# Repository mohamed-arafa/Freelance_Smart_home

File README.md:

# Freelance_Smart_home
Arduino Nano code &amp; PCB design

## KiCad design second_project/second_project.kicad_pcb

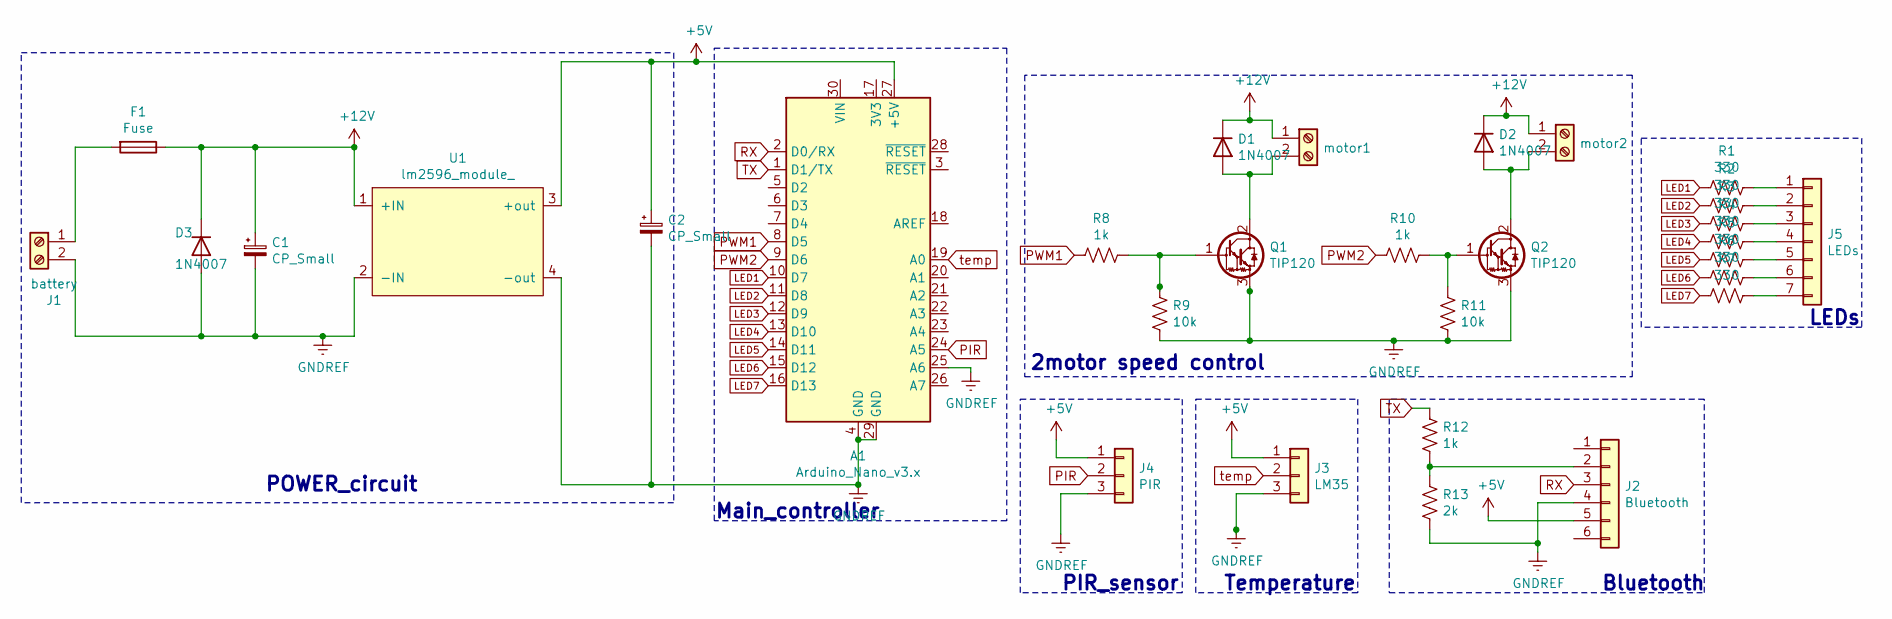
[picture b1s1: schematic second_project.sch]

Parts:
A1: Arduino_Nano_v3.x; Arduino_Nano
C1, C2: CP_Small; CP_Radial_D8.0mm_P3.80mm
D1, D2, D3: 1N4007; D_DO-41_SOD81_P10.16mm_Horizontal
F1: Fuse; Fuse_clips_20x5_pair
J1: battery; TerminalBlock_Phoenix_MKDS-1,5-2-5.08_1x02_P5.08mm_Horizont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
J2: Bluetooth; PinSocket_1x06_P2.54mm_Vertical
J3: LM35; PinSocket_1x03_P2.54mm_Vertical
J4: PIR; PinSocket_1x03_P2.54mm_Vertical
J5: LEDs; PinHeader_1x07_P2.54mm_Vertical
Q1, Q2: TIP120; TO-220-3_Vertical
R1, R2, R3, R4, R5, R6, R7: 330; R_Axial_DIN0207_L6.3mm_D2.5mm_P10.16mm_Horizontal
R8, R10, R12: 1k; R_Axial_DIN0207_L6.3mm_D2.5mm_P10.16mm_Horizontal
R9, R11: 10k; R_Axial_DIN0207_L6.3mm_D2.5mm_P10.16mm_Horizontal
R13: 2k; R_Axial_DIN0207_L6.3mm_D2.5mm_P10.16mm_Horizontal
U1: lm2596_module_; lm2596
motor1, motor2: Screw_Terminal_01x02; TerminalBlock_Phoenix_MKDS-1,5-2-5.08_1x02_P5.08mm_Horizont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

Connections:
+5V: A1.27 (+5V), C2.1, J2.5, J3.1, J4.1, U1.3 (+out)
+12V: C1.1, D1.1 (K), D2.1 (K), D3.1 (K), F1.1, U1.1 (+IN), motor1.1, motor2.1
GNDREF: A1.4 (GND), A1.25 (A6), A1.29 (GND), C1.2, C2.2, D3.2 (A), J1.2, J2.4, J3.3, J4.3, Q1.3 (E), Q2.3 (E), R9.1, R11.1, R13.2, U1.2 (-IN), U1.4 (-out)
LED1: A1.10 (D7), R1.2
LED2: A1.11 (D8), R2.2
LED3: A1.12 (D9), R3.2
LED4: A1.13 (D10), R4.2
LED5: A1.14 (D11), R5.2
LED6: A1.15 (D12), R6.2
LED7: A1.16 (D13), R7.2
unnamed: D1.2 (A), Q1.2 (C), motor1.2
unnamed: D2.2 (A), Q2.2 (C), motor2.2
unnamed: F1.2, J1.1
unnamed: J2.2, R12.2, R13.1
unnamed: J5.1, R1.1
unnamed: J5.2, R2.1
unnamed: J5.3, R3.1
unnamed: J5.4, R4.1
unnamed: J5.5, R5.1
unnamed: J5.6, R6.1
unnamed: J5.7, R7.1
unnamed: Q1.1 (B), R8.1, R9.2
unnamed: Q2.1 (B), R10.1, R11.2
PIR: A1.24 (A5), J4.2
PWM1: A1.8 (D5), R8.2
PWM2: A1.9 (D6), R10.2
RX: A1.2 (D0/RX), J2.3
TX: A1.1 (D1/TX), R12.1
temp: A1.19 (A0), J3.2

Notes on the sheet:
Bluetooth
2motor speed control
Temperature
PIR_sensor
POWER_circuit
Main_controller
LEDs

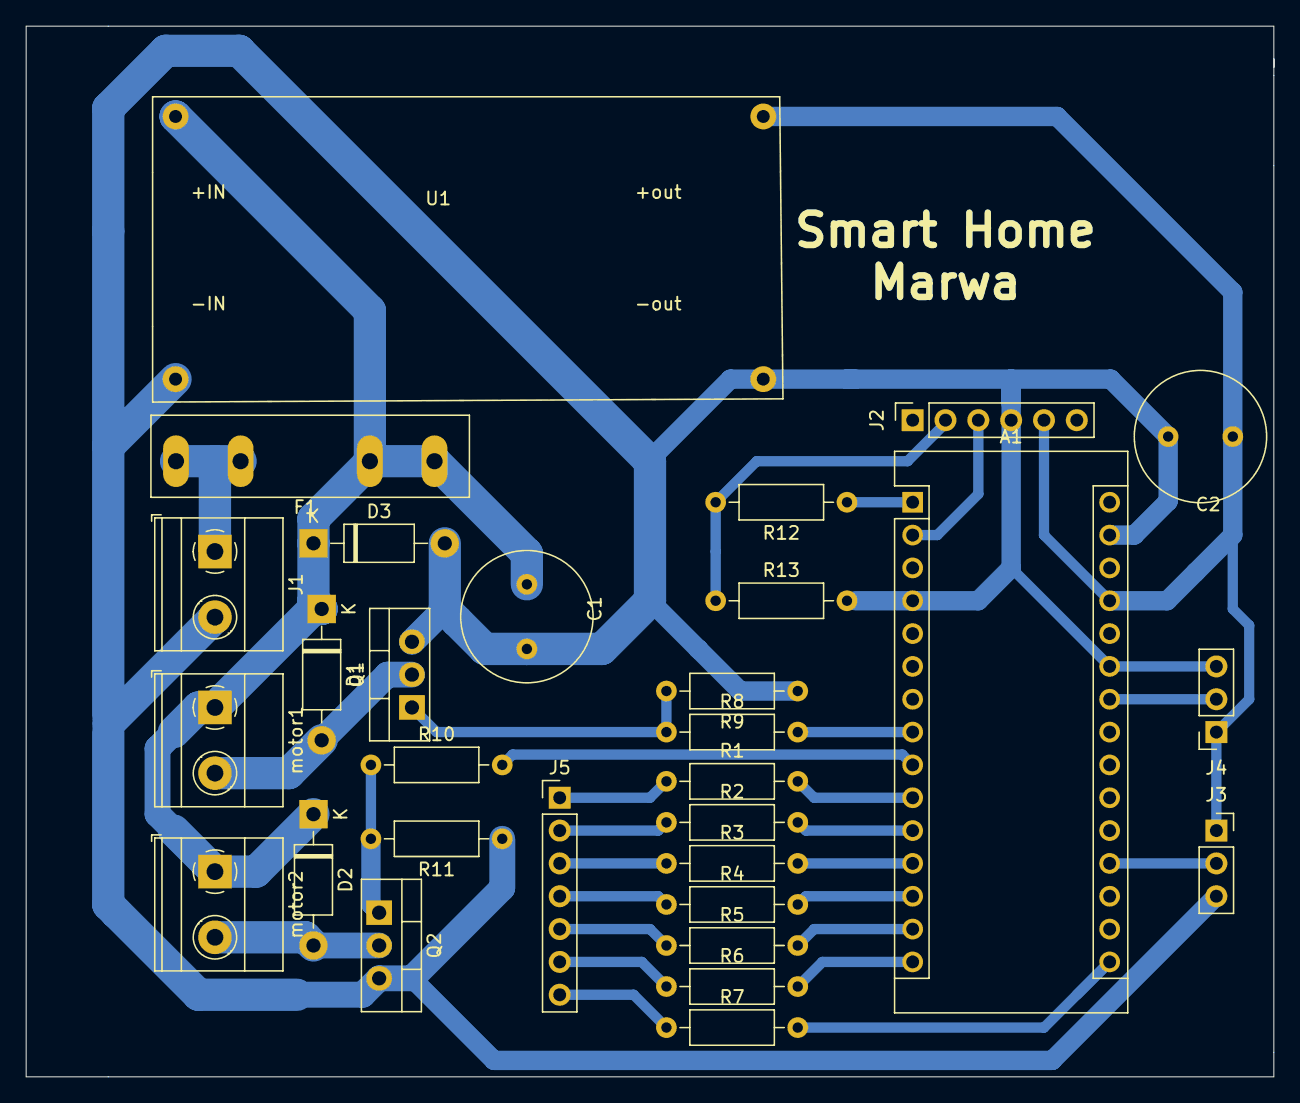
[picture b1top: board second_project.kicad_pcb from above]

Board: 2 copper layers, 96.5 x 81.3 mm, 30 parts (0 on the bottom side), 29 nets.
